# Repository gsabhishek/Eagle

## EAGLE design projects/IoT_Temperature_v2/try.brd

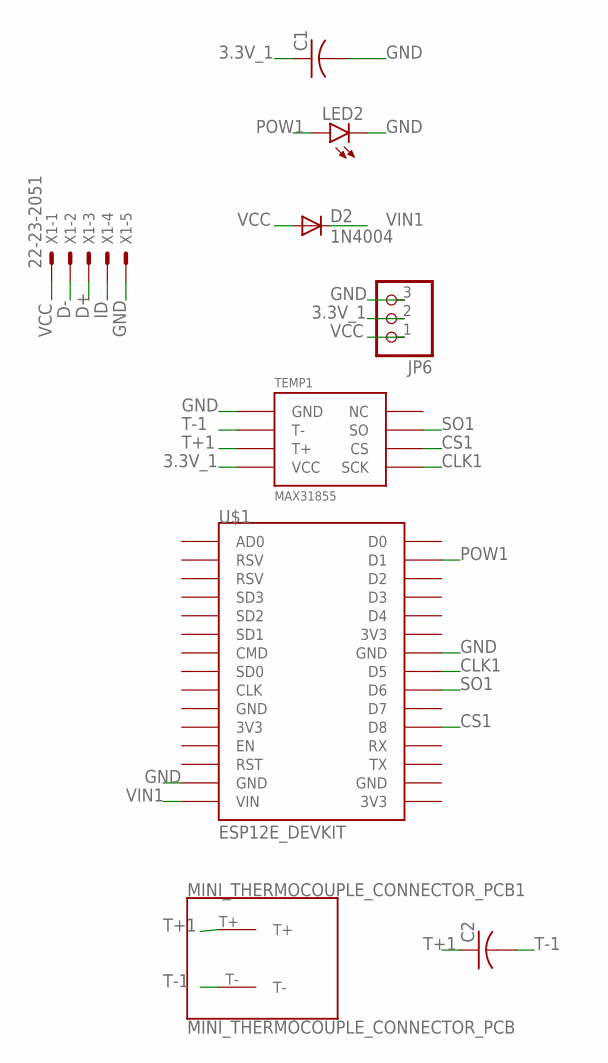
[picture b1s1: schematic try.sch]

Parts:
C1, C2: C-US025-040X050; C025-040X050
D2: 1N4004; DO41-10
JP6: PINHD-1X3CB; 1X03-CLEANBIG
LED2: LED5MM
MINI_THERMOCOUPLE_CONNECTOR_PCB1: MINI_THERMOCOUPLE_CONNECTOR_PCB
TEMP1: MAX31855; SOIC-8
U$1: ESP12E_DEVKIT
X1: 22-23-2051

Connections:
3.3V_1: C1.1, JP6.2, TEMP1.VCC
CLK1: TEMP1.SCK, U$1.D5
CS1: TEMP1.CS, U$1.D8
D+: X1.3
D-: X1.2
GND: C1.2, JP6.3, LED2.K (C), TEMP1.GND, U$1.GND@1 (GND), U$1.GND@2 (GND), X1.5
ID: X1.4
POW1: LED2.A, U$1.D1
SO1: TEMP1.SO, U$1.D6
T+1: C2.1, MINI_THERMOCOUPLE_CONNECTOR_PCB1.T+, TEMP1.T+
T-1: C2.2, MINI_THERMOCOUPLE_CONNECTOR_PCB1.T-, TEMP1.T-
VCC: D2.A, JP6.1, X1.1
VIN1: D2.C, U$1.VIN

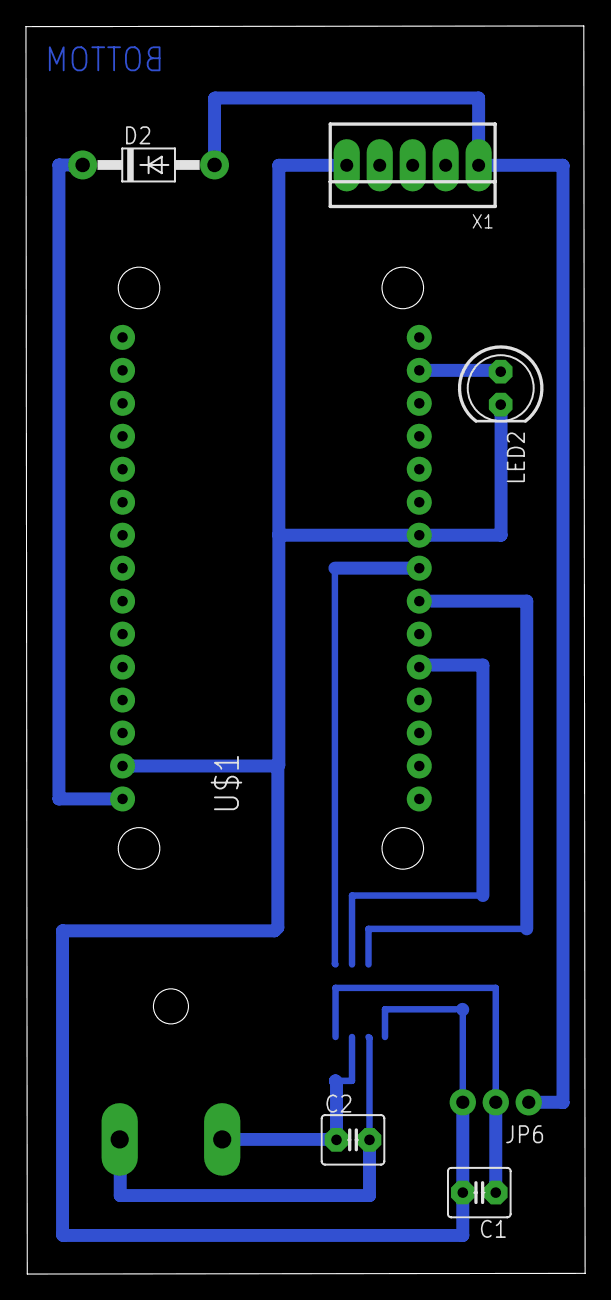
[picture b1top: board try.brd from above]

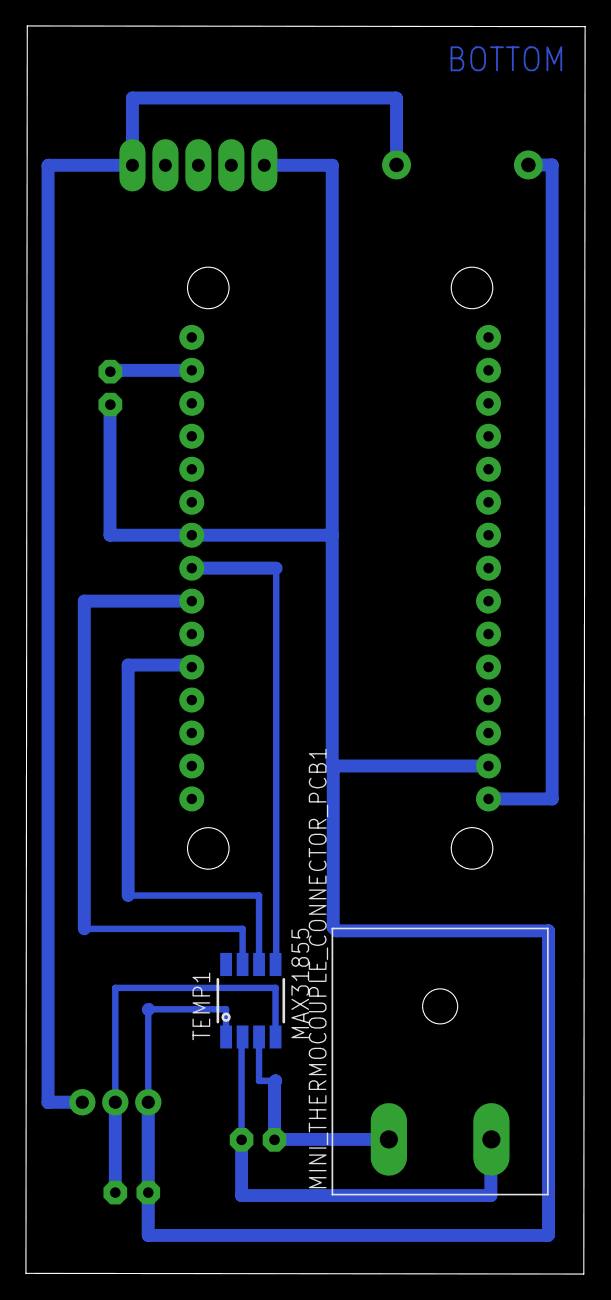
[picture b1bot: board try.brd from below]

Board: 2 copper layers, 43.1 x 96.2 mm, 9 parts (2 on the bottom side), 10 nets.

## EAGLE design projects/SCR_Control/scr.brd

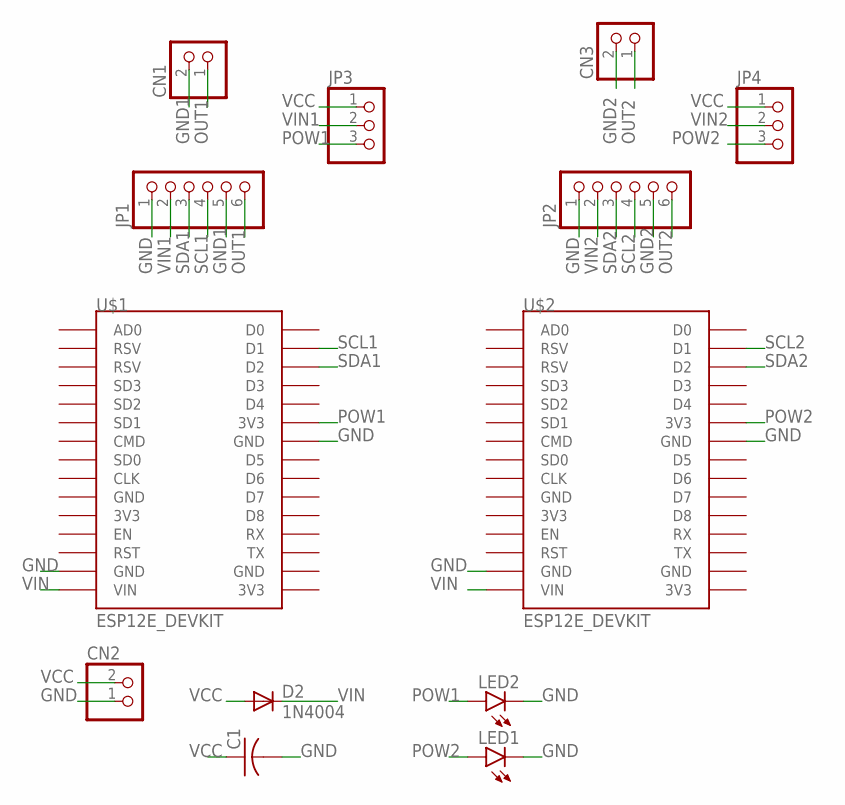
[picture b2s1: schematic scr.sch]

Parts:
C1: C-US025-040X050; C025-040X050
CN1, CN2, CN3: JST_2PIN-THM; JST-PH-2-THM
D2: 1N4004; DO41-10
JP1, JP2: PINHD-1X6; 1X06
JP3, JP4: PINHD-1X3CB; 1X03-CLEANBIG
LED1, LED2: LED5MM
U$1, U$2: ESP12E_DEVKIT

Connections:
GND: C1.2, CN2.1 (2), JP1.1, JP2.1, LED1.K (C), LED2.K (C), U$1.GND@1 (GND), U$1.GND@2 (GND), U$2.GND@1 (GND), U$2.GND@2 (GND)
GND1: CN1.2 (1), JP1.5
GND2: CN3.2 (1), JP2.5
OUT1: CN1.1 (2), JP1.6
OUT2: CN3.1 (2), JP2.6
POW1: JP3.3, LED2.A, U$1.3V3@1 (3V3)
POW2: JP4.3, LED1.A, U$2.3V3@1 (3V3)
SCL1: JP1.4, U$1.D1
SCL2: JP2.4, U$2.D1
SDA1: JP1.3, U$1.D2
SDA2: JP2.3, U$2.D2
VCC: C1.1, CN2.2 (1), D2.A, JP3.1, JP4.1
VIN: D2.C, U$1.VIN, U$2.VIN
VIN1: JP1.2, JP3.2
VIN2: JP2.2, JP4.2

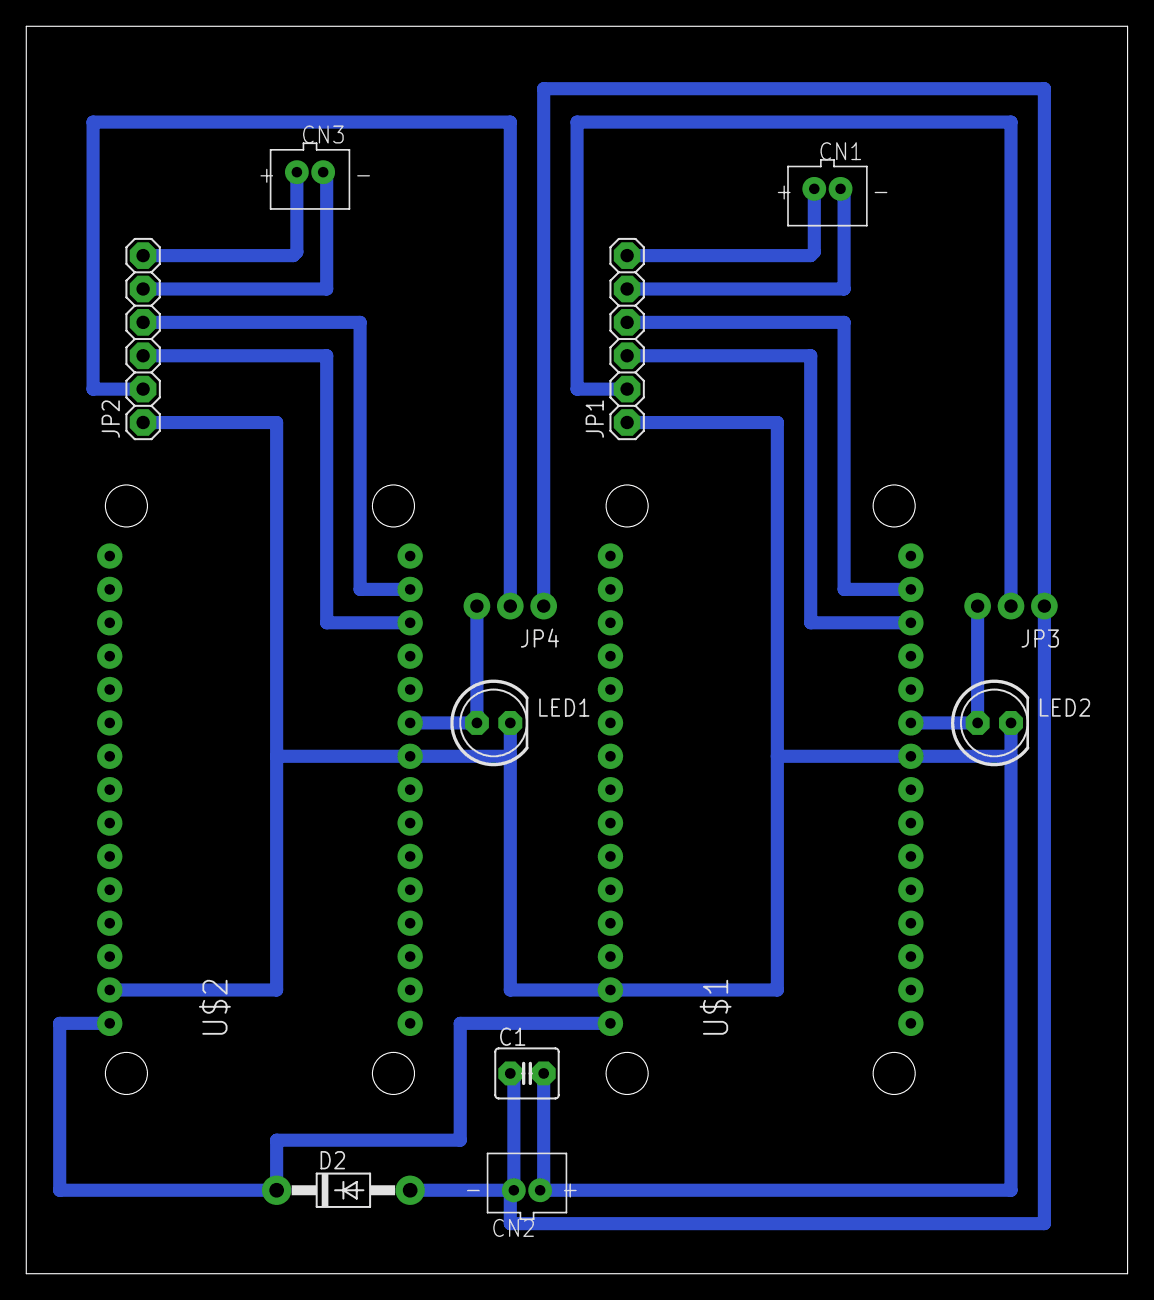
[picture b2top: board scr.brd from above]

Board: 2 copper layers, 83.8 x 94.9 mm, 13 parts (0 on the bottom side), 15 nets.

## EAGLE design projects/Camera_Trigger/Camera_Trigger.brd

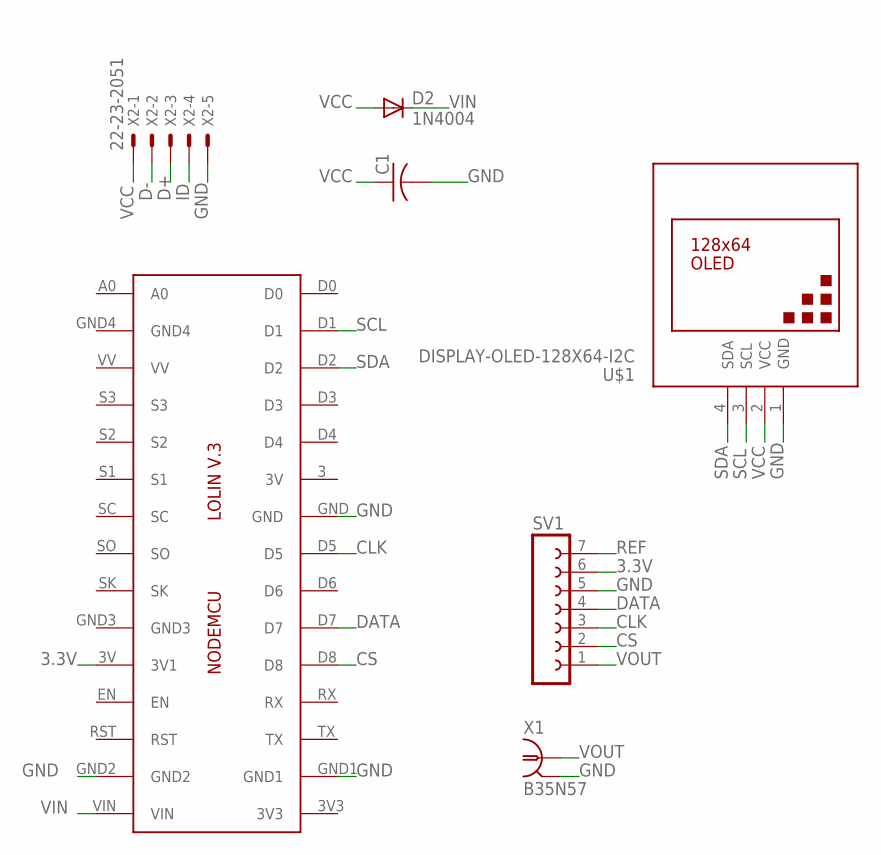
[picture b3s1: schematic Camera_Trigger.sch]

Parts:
C1: C-US025-040X050; C025-040X050
D2: 1N4004; DO41-10
IC1: LOLINV3
SV1: FE07-1; FE07
U$1: DISPLAY-OLED-128X64-I2C
X1: B35N57
X2: 22-23-2051

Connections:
3.3V: IC1.3V (3V1), SV1.6
CLK: IC1.D5, SV1.3
CS: IC1.D8, SV1.2
D+: X2.3
D-: X2.2
DATA: IC1.D7, SV1.4
GND: C1.2, IC1.GND, IC1.GND1, IC1.GND2, SV1.5, U$1.1 (GND), X1.2, X1.3 (2), X1.4 (2), X1.5 (2), X2.5
ID: X2.4
REF: SV1.7
SCL: IC1.D1, U$1.3 (SCL)
SDA: IC1.D2, U$1.4 (SDA)
VCC: C1.1, D2.A, U$1.2 (VCC), X2.1
VIN: D2.C, IC1.VIN
VOUT: SV1.1, X1.1

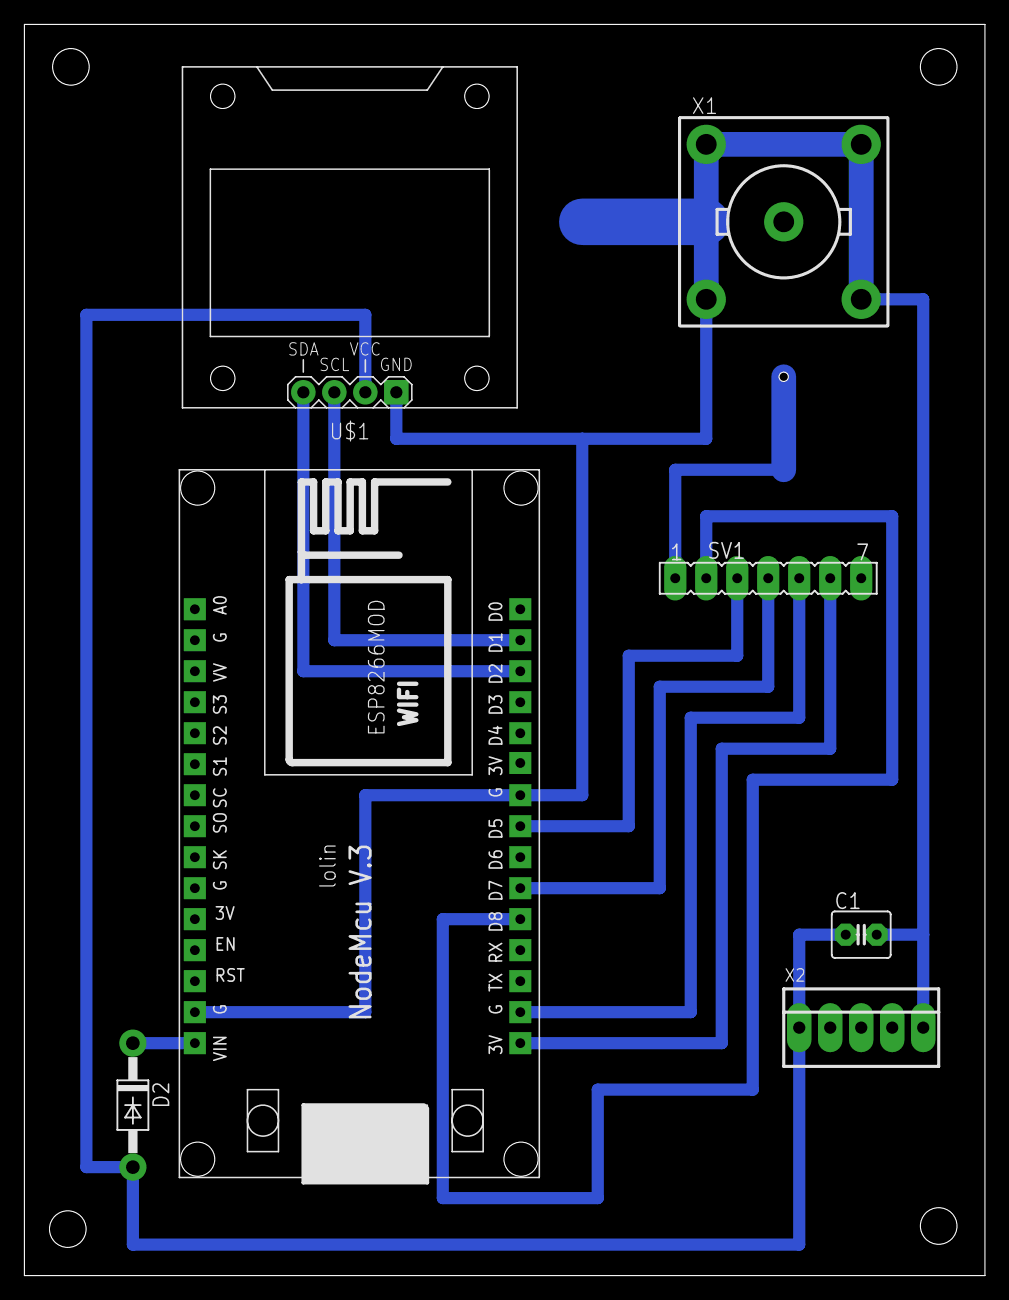
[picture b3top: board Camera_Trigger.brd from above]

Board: 2 copper layers, 78.7 x 102.5 mm, 7 parts (0 on the bottom side), 10 nets.

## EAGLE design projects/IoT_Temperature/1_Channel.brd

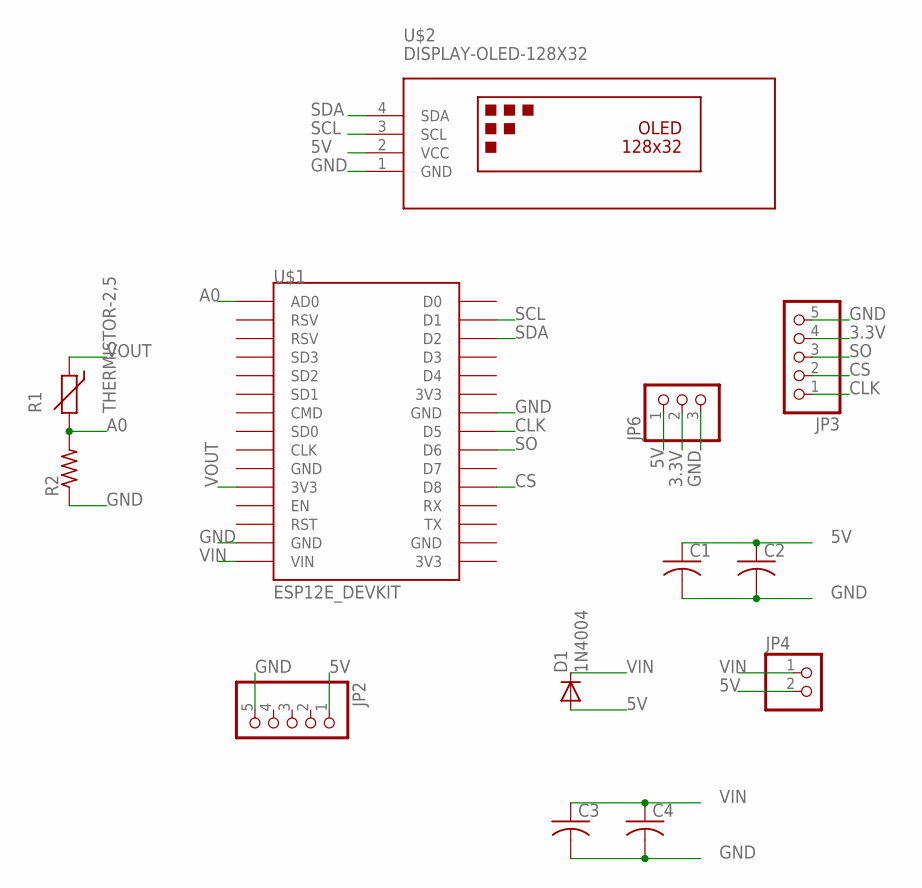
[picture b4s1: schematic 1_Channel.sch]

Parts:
C1, C2, C3, C4: C-US050-025X075; C050-025X075
D1: 1N4004; DO41-10
JP2, JP3: PINHD-1X5; 1X05
JP4: PINHD-1X2; 1X02
JP6: PINHD-1X3CB; 1X03-CLEANBIG
R1: THERMISTOR-2,5; RS-2,5
R2: R-US_0207/7; 0207/7
U$1: ESP12E_DEVKIT
U$2: DISPLAY-OLED-128X32

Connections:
3.3V: JP3.4, JP6.2
5V: C1.1, C2.1, D1.A, JP2.1, JP4.2, JP6.1, U$2.2 (VCC)
A0: R1.2, R2.2, U$1.AD0
CLK: JP3.1, U$1.D5
CS: JP3.2, U$1.D8
GND: C1.2, C2.2, C3.2, C4.2, JP2.5, JP3.5, JP6.3, R2.1, U$1.GND@1 (GND), U$1.GND@2 (GND), U$2.1 (GND)
SCL: U$1.D1, U$2.3 (SCL)
SDA: U$1.D2, U$2.4 (SDA)
SO: JP3.3, U$1.D6
VIN: C3.1, C4.1, D1.C, JP4.1, U$1.VIN
VOUT: R1.1, U$1.3V3@0 (3V3)

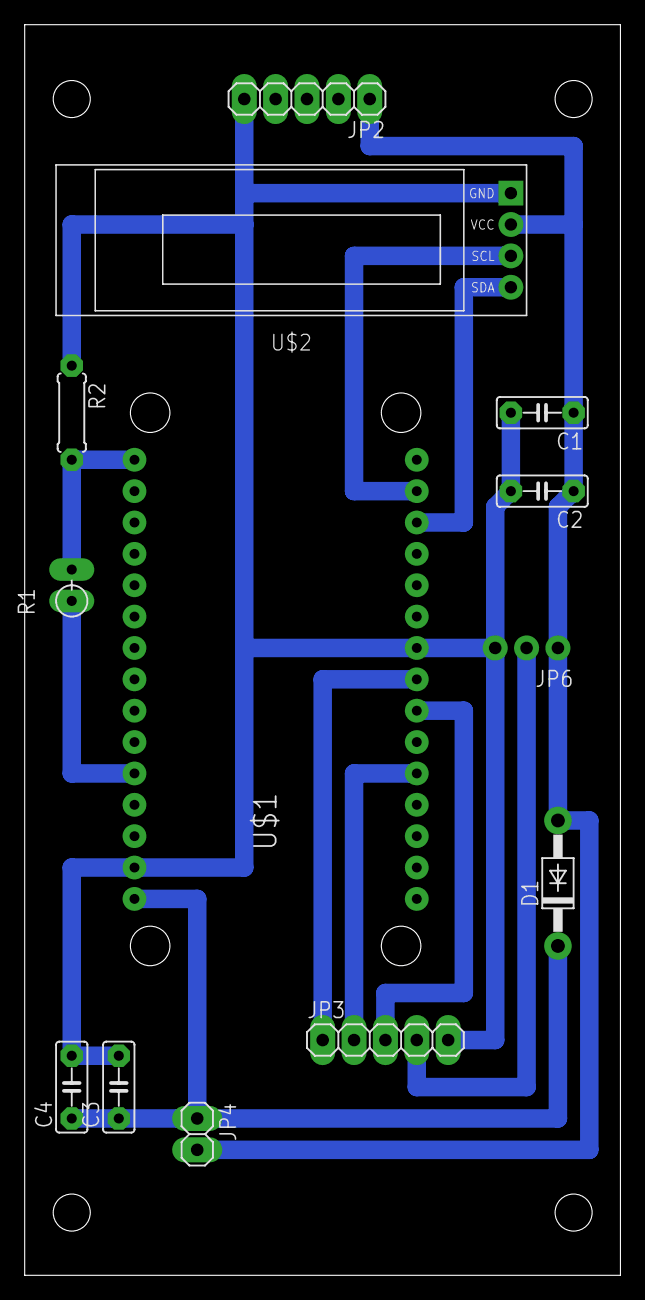
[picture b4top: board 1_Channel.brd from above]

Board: 2 copper layers, 48.2 x 101.3 mm, 13 parts (0 on the bottom side), 11 nets.

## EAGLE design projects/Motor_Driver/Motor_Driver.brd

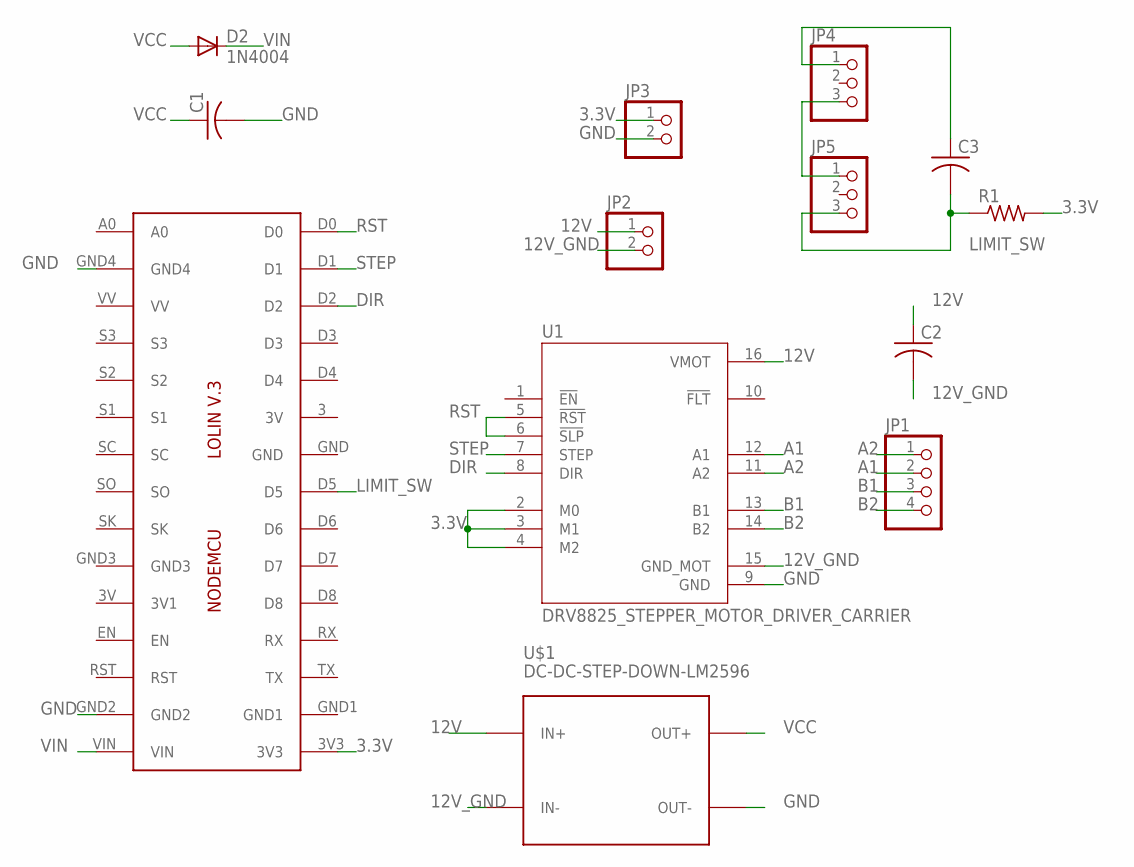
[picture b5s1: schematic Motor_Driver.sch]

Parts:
C1: C-US025-040X050; C025-040X050
C2, C3: C-US050-035X075; C050-035X075
D2: 1N4004; DO41-10
IC1: LOLINV3
JP1: PINHD-1X4; 1X04
JP2, JP3: PINHD-1X2; 1X02
JP4, JP5: PINHD-1X3CB; 1X03-CLEANBIG
R1: R-US_V234/12; V234/12
U1: DRV8825_STEPPER_MOTOR_DRIVER_CARRIER; IC_DRV8825_STEPPER_MOTOR_DRIVER_CARRIER
U$1: DC-DC-STEP-DOWN-LM2596

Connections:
3.3V: IC1.3V3, JP3.1, R1.2, U1.2 (M0), U1.3 (M1), U1.4 (M2)
12V: C2.1, JP2.1, U1.16 (VMOT), U$1.IN+
12V_GND: C2.2, JP2.2, U1.15 (GND_MOT), U$1.IN-
A1: JP1.2, U1.12 (A1)
A2: JP1.1, U1.11 (A2)
B1: JP1.3, U1.13 (B1)
B2: JP1.4, U1.14 (B2)
DIR: IC1.D2, U1.8 (DIR)
GND: C1.2, IC1.GND2, IC1.GND4, JP3.2, U1.9 (GND), U$1.OUT-
LIMIT_SW: C3.2, IC1.D5, JP5.3, R1.1
unnamed: JP4.3, JP5.1
unnamed: C3.1, JP4.1
RST: IC1.D0, U1.5 (!RST), U1.6 (!SLP)
STEP: IC1.D1, U1.7 (STEP)
VCC: C1.1, D2.A, U$1.OUT+
VIN: D2.C, IC1.VIN

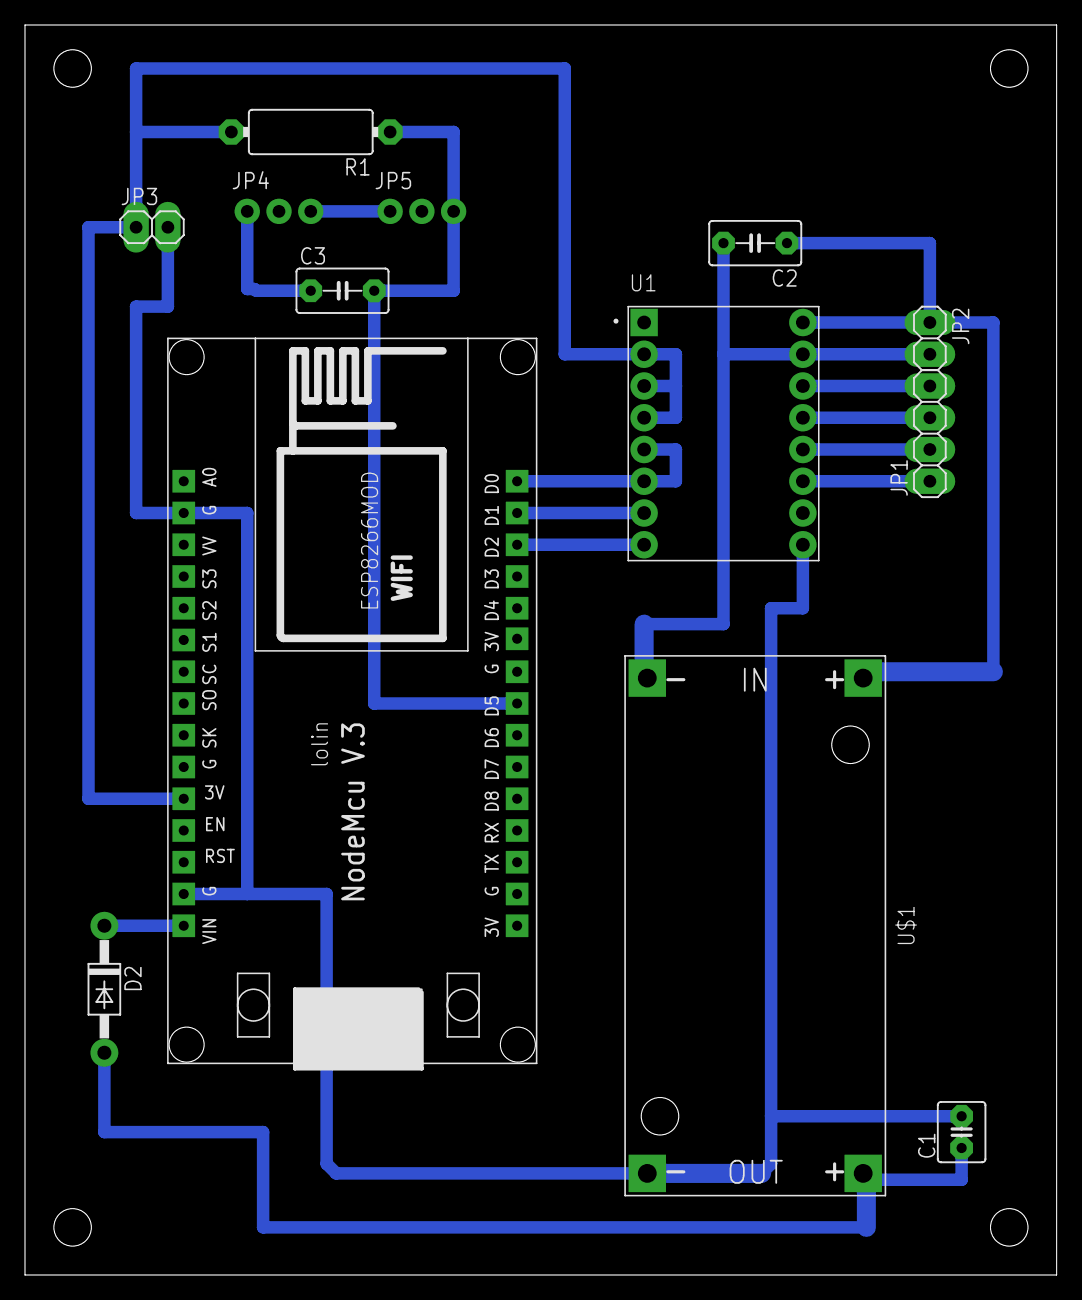
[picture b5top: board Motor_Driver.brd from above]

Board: 2 copper layers, 82.5 x 100.0 mm, 13 parts (0 on the bottom side), 16 nets.

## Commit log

2020-04-02 Adding New Libraries
    Lolin NodeMCU and Stepper Motor Driver DRV8825
2020-04-02 Adding all projects

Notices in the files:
parts and their libraries:
diy-modules: Released under the Creative Commons Attribution 4.0 International License: http://creativecommons.org/licenses/by/4.0
